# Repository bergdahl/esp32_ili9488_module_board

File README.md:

# esp32_ili9488_module_board

> This is a work in progress. 

This is a simple ESP32 based board for the _3.5" TFT SPI 480X320_ module. It is powered by 5V over a 
micro USB connector, and has footprints both for ESP-WROOM-32 and ESP_VROVER-32.

I designed the board primarily for use with [Dustin Watt's FreeTouchDeck firmware](https://github.com/DustinWatts/FreeTouchDeck).

Programming is done using an external FTDI232 board.

## PCB files

I have added the Gerber files in the `PCB/Gerber` folder, just zip and upload to your favorite PCB manufacturer.

I have also included the EAGLE design files if you need to modify the design for yoyr needs.

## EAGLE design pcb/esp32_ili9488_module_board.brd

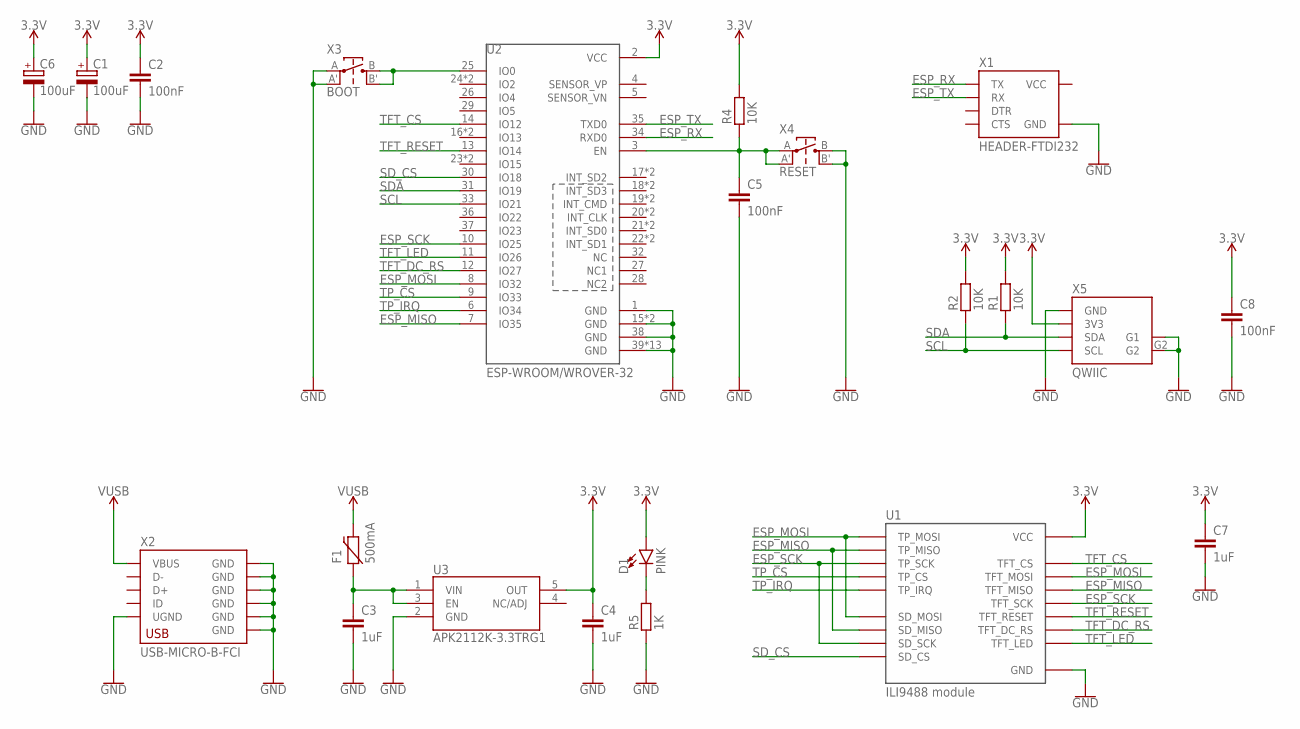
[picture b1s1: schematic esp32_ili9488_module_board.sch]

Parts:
C1, C6: 100uF; PANASONIC-SV-C
C2, C5, C8: 100nF; C0603
C3, C4, C7: 1uF; C0603
D1: PINK; LED0603
F1: 500mA; PTC-0ZCJ-1206
R1, R2, R4: 10K; R0603
R5: 1K; R0603
U1: ILI9488 module; TFT-ILI9488-MODULE
U2: ESP-WROOM/WROVER-32; ESP-WROOM_WROVER-32
U3: APK2112K-3.3TRG1; SOT23-5
X1: HEADER-FTDI232; FTDI232-1X06
X2: USB-MICRO-B-FCI
X3: BOOT; TACT-SWITCH-EVQ
X4: RESET; TACT-SWITCH-EVQ
X5: QWIIC; JST-SH-4-SMD-RA

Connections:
3.3V: C1.+, C2.1, C4.1, C6.+, C7.1, C8.1, D1.A, R1.2, R2.2, R4.2, U1.VCC, U2.2 (VCC), U3.5 (OUT), X5.3V3
ESP_MISO: U1.SD_MISO, U1.TFT_MISO, U1.TP_MISO, U2.7 (IO35)
ESP_MOSI: U1.SD_MOSI, U1.TFT_MOSI, U1.TP_MOSI, U2.8 (IO32)
ESP_RX: U2.34 (RXD0), X1.TX
ESP_SCK: U1.SD_SCK, U1.TFT_SCK, U1.TP_SCK, U2.10 (IO25)
ESP_TX: U2.35 (TXD0), X1.RX
GND: C1.-, C2.2, C3.2, C4.2, C5.2, C6.-, C7.2, C8.2, R5.1, U1.GND, U2.1 (GND), U2.15 (GND), U2.15_R (GND), U2.38 (GND), U2.39 (GND), U2.39V_1 (GND), U2.39V_2 (GND), U2.39V_3 (GND), U2.39V_4 (GND), U2.39V_5 (GND), U2.39V_6 (GND), U2.39V_7 (GND), U2.39V_8 (GND), U2.39V_9 (GND), U2.39V_10 (GND), U2.39V_12 (GND), U2.39V_13 (GND), U3.2 (GND), X1.GND, X2.5 (UGND), X2.GND@1 (GND), X2.GND@2 (GND), X2.GND@3 (GND), X2.GND@4 (GND), X2.GND@5 (GND), X2.GND@6 (GND), X3.A, X3.A', X4.B, X4.B', X5.G1, X5.G2, X5.GND
unnamed: C3.1, F1.1, U3.1 (VIN), U3.3 (EN)
unnamed: D1.C, R5.2
unnamed: C5.1, R4.1, U2.3 (EN), X4.A, X4.A'
unnamed: U2.25 (IO0), X3.B, X3.B'
SCL: R2.1, U2.33 (IO21), X5.SCL
SDA: R1.1, U2.31 (IO19), X5.SDA
SD_CS: U1.SD_CS, U2.30 (IO18)
TFT_CS: U1.TFT_CS, U2.14 (IO12)
TFT_DC_RS: U1.TFT_DC_RS, U2.12 (IO27)
TFT_LED: U1.TFT_LED, U2.11 (IO26)
TFT_RESET: U1.TFT_RESET, U2.13 (IO14)
TP_CS: U1.TP_CS, U2.9 (IO33)
TP_IRQ: U1.TP_IRQ, U2.6 (IO34)
VCC: X1.VCC
VUSB: F1.2, X2.1 (VBUS)

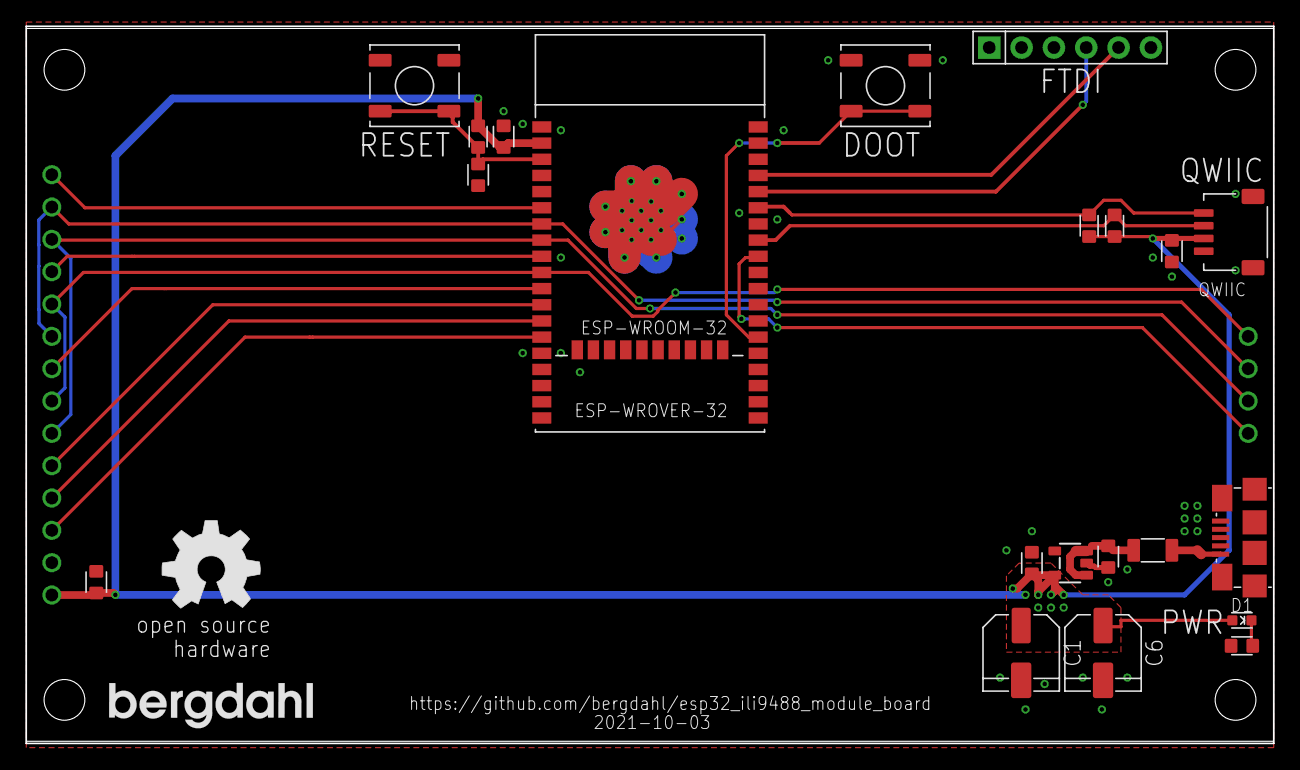
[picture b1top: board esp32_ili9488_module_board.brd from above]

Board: 2 copper layers, 98.0 x 56.3 mm, 24 parts (1 on the bottom side), 21 nets.

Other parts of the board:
U$1: BERGDAHL-20MM-TPLACE
U$2: OSHW-8MM-TPLACE

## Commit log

2021-10-03 Added schematic PDF
2021-10-03 Add I2C pullups
2021-10-03 Updated gerbers
